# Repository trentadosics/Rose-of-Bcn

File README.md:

# Rose-of-Bcn
PCB-Art with KiCAD workshop (FAB-Casa del Mig, Barcelona) - June 2026

In collaboration with: FAB - Casa del Mig (Barcelona; Oriol Blas, Ricard Gómez and Neus Martínez)

<table>
  <tr>
    <td width="220">
      
    </td>
    <td>
      <h2>Description</h2>
      <p>
        This educational project was designed to teach the fundamentals of PCB layout design using KiCad, along with Inkscape for the graphical design of the PCB.
      </p>
      <p>
        By the end of the workshop, participants have a complete digital design of a pendant PCB featuring the Rose of Barcelona, ready to be ordered.
      </p>
      <p>
        The pendant includes an LED around its outline that lights up whenever it is moved or shaken.
      </p>
      <p>
        This design is also available on PCBWay:
        <a href="https://www.pcbway.com/project/shareproject/Flor_de_Barcelona_PCB_2439f1df.html">
          View on PCBWay
        </a>
      </p>
    </td>
  </tr>
</table>

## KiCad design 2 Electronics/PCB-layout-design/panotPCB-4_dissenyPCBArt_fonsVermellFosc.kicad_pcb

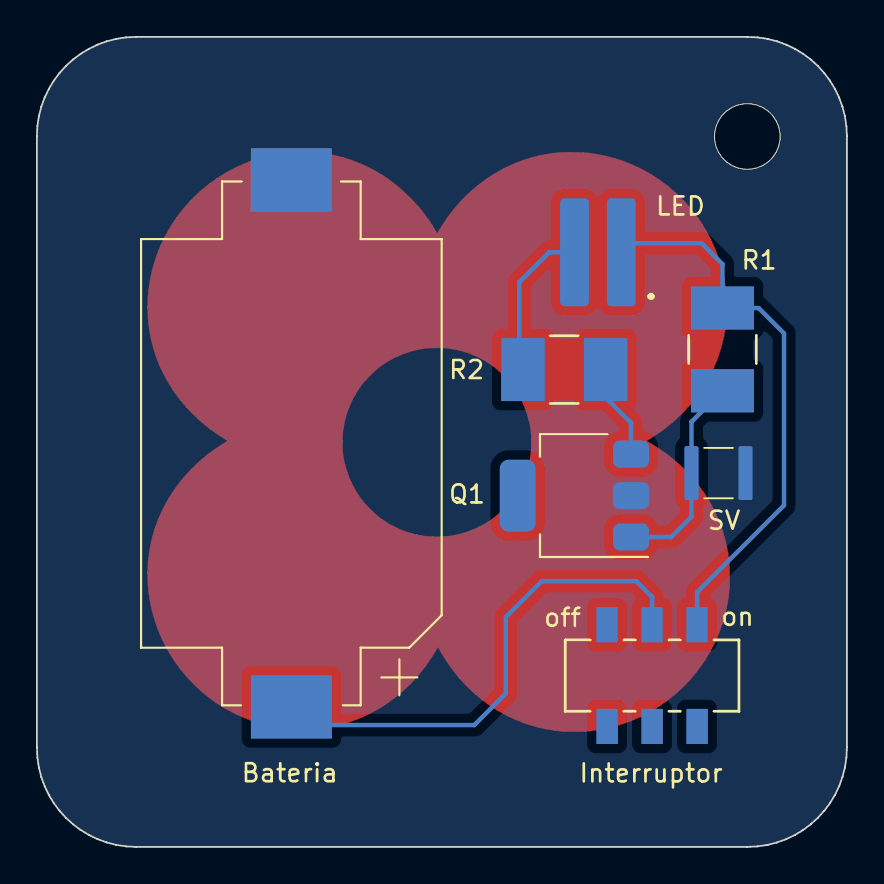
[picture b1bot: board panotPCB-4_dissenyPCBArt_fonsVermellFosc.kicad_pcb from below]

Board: 2 copper layers, 45.0 x 45.0 mm, 7 parts (7 on the bottom side), 6 nets.

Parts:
BT1: 3V; 1060_3VCR2032_SMD
D1: LED; LEDCOB-flexible-filament-SMD
Q1: NPN; P205_SOT-223
R1: 10K; RES_73M2A1-4mOHM_CTS
R2: 120R; RES_73M2A1-4mOHM_CTS
SW1: SLW-913535-2A-SMT; SLW-913535_CUD
TD-1210-X3228-A1: Sensor Vibració; TD-1210-X3228-A1

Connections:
GND: BT1.2 (-), Q1.2 (E), TD-1210-X3228-A1.2
unnamed: BT1.1 (+), SW1.5
unnamed: D1.2 (A), R1.1, SW1.6
unnamed: D1.1 (K), R2.1
unnamed: Q1.1 (B), R1.2, TD-1210-X3228-A1.1
unnamed: Q1.3 (C), R2.2
